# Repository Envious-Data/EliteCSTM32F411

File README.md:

# EliteCSTM32F411
 A STM32F411 board with the pinout of an Elite-C

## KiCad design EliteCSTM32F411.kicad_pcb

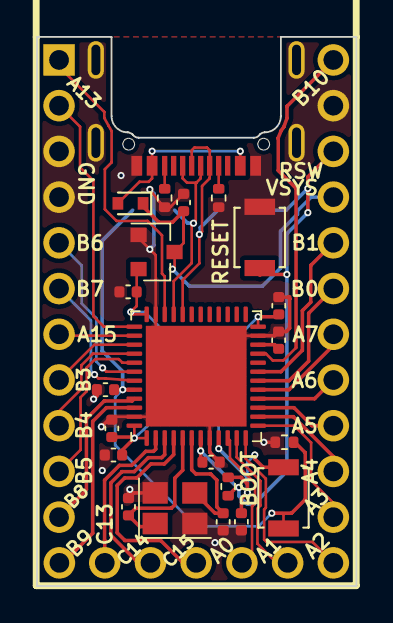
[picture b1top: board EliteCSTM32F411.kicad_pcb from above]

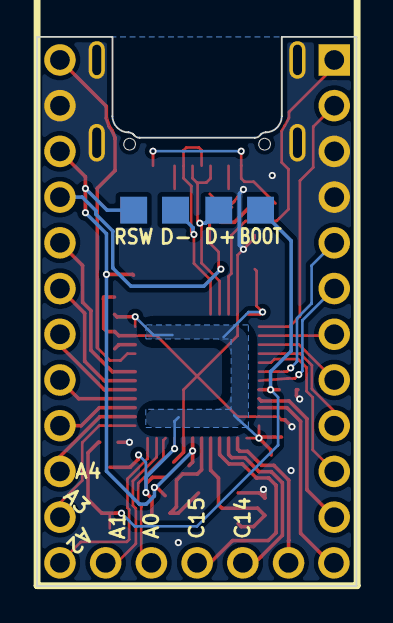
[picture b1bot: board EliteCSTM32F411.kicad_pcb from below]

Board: 2 copper layers, 17.8 x 30.5 mm, 27 parts (4 on the bottom side), 37 nets.

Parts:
C1: 2.2uF 0402; C_0402_1005Metric
C2, C3, C4, C5: 100nf capacitor; C_0402_1005Metric
C6, C7: 1uf capacitor; C_0402_1005Metric
C8, C9: 100nf 0402; C_0402_1005Metric
C10, C11: 22pf capacitor; C_0402_1005Metric
D1: General Purpose diode SOD-523; D_SOD-523
R1, R2: 5.1K 0402; R_0402_1005Metric
R6: 10K 0402; R_0402_1005Metric
R7: 100k 0402; R_0402_1005Metric
SW1: Boot Mode; SW_SPST_B3U-1000P
SW2: Reset Switch; SW_SPST_B3U-1000P
TP1, TP2, TP3, TP4: TestPoint; CustomTestPoint
U1: STM32F411CEUx; QFN-48-1EP_7x7mm_P0.5mm_EP5.6x5.6mm
U2: XC6206PxxxMR; SOT-23
U3: Elite-C
USB1: HRO-TYPE-C-31-M-14; USB_C_TYPE-C-31-M-14
Y1: 8Mhz 3225; Crystal_SMD_3225-4Pin_3.2x2.5mm

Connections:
+3V3: C2.1, C3.2, C4.2, C5.2, C7.2, R6.2, SW1.1, U1.1, U1.9, U1.24, U1.36, U1.48, U2.2
D+: TP2.1, U1.33, USB1.A6, USB1.B6
D-: TP1.1, U1.32, USB1.A7, USB1.B7
GND: C1.1, C2.2, C3.1, C4.1, C5.1, C6.1, C7.1, C8.2, C9.2, C10.2, C11.2, R1.1, R2.1, R7.2, SW2.1, U1.8, U1.23, U1.35, U1.47, U1.49, U2.1, U3.3, U3.4, U3.23, USB1.A1, USB1.A12, USB1.B1, USB1.B12, USB1.S1, Y1.2, Y1.4
unnamed: C1.2, U1.22
unnamed: R1.2, USB1.A5
unnamed: R2.2, USB1.B5
OSCIN: C10.1, U1.5, Y1.1
OSCOUT: C11.1, U1.6, Y1.3
PA0: U1.10, U3.28
PA1: U1.11, U3.29
PA2: U1.12, U3.13
PA3: U1.13, U3.14
PA4: U1.14, U3.15
PA5: U1.15, U3.16
PA6: U1.16, U3.17
PA7: U1.17, U3.18
PA13-SWDIO: U1.34, U3.1
PA14-SWCLK: U1.37, U3.2
PA15: U1.38, U3.7
PB0: U1.18, U3.19
PB1: U1.19, U3.20
PB3: U1.39, U3.8
PB4: U1.40, U3.9
PB5: U1.41, U3.10
PB6: U1.42, U3.5
PB7: U1.43, U3.6
PB8: U1.45, U3.11
PB9: U1.46, U3.12
PB10: U1.21, U3.24
PC13: U1.2, U3.25
PC14: U1.3, U3.26
PC15: U1.4, U3.27
VBUS: D1.2, USB1.A4, USB1.A9, USB1.B4, USB1.B9
VSYS: C6.2, D1.1, U2.3, U3.21
boot0: C8.1, R7.1, SW1.2, TP4.1, U1.44
resetsw: C9.1, R6.1, SW2.2, TP3.1, U1.7, U3.22

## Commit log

2022-01-12 Initial Commit +1
2022-01-12 redid some pins, i2c compatible with pro micro. (also redid some labels)
